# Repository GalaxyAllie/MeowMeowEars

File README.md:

# Meow Meow Ears

This is a project to create a pair of programmable neko mimis that feature ten LEDs.

## WARNINGS - *max power draw* and *brightness* and *health*

Please be aware that the LEDs can *easily* exceed the max power draw of this circuit design. It is highly recommended not to exceed 150 mA. They're cat ears, you don't need to blind everyone - keep the NeoPixel library brightness down to around 50 or so, tops :)

Also be aware some people are *photo sensitive* - these are meant for rave environments. For environments where people may not expect flashing lights (and where they do...) *please be considerate*.

## Basic Features

- ATSAMD21 microcontroller (ARM Cortext M0)
- Ten WS2812b RGB LEDs
- Power and status LEDs
- One capacitive touch zone - though this isn't used in the example code
- Native USB (you can even use it as a keyboard, hopefully)
- Designed to be put in cat ear headbands. Meow!
- Probably a fair number of bugs and bad design decisions!

## Copyright/Liability

I licence this work under [CC BY-SA 4.0](https://creativecommons.org/licenses/by-sa/4.0/#)

Also, I'm obviously not responsible for injuries or anything like that - this is definitely not a safety-tested, commercial project. Build at your own risk. It probably won't even work :)

## Build Notes

You really shouldn't draw over 50 mA or so of power, you're probably blinding people if you do :) - see warnings above. Thus, you should be fine to input all the way up to the linear regulator max voltage rating of 6V - but you're wasting energy over 3.3V. Thus, 3x NiMH batteries or a 3.7V Lion battery would be good power choices - be smart and sensible though. Batteries can be dangerous. There is no hardware over-discharge protection, so use only batteries with this protection!

Boards can be ordered from [Osh Park](https://oshpark.com/shared_projects/LssyuQtY) - that's not an affiliate link or anything, just a convenient source. And they're purple.

I have forked and modified the Adafruit Trinket M0 file from the Microsoft USB Mass Storage [Bootloader](https://github.com/MermaidAllie/uf2-samdx1/tree/master/build/alliecat_meowmeowears) for the ATSAMD21. The Trinket M0 bootloader also works, tho!

## Bill of Materials

| Component                               | Manufacturer                 | Qty |
|-----------------------------------------|------------------------------|-----|
| This board                              | Whoever you choose           | 1   |
| ATSAMD21E18A-AU-ND                      | Microchip Technology         | 1   |
| S2B-PH-SM4-TB(LF)(SN)                   | JST                          | 1   |
| 0.1uF 0603 Capacitor                    | Any                          | 10  |
| 1uF 0603 Capacitor                      | Any                          | 2   |
| 10uF 0603 Capacitor                     | Any                          | 2   |
| WS2812b LED                             | Worldsemi                    | 10  |
| UV/blacklight LED 0805 (or fave :) )    | Generic                      | 2   |
| AP2112K-3.3TRG1                         | Diodes Incorporated          | 1   |
| BAT54-TP                                | Micro Commercial Co          | 2   |
| USB3076-30-A                            | GCT                          | 1   |
| 510 Ohm 0805 Resistor (diff if UV sub)  | Any                          | 2   |
| 330 Ohm 0805 Resistor                   | Any                          | 1   |
| 3.5 x 6 mm push button switch           | Generic                      | 1   |

## Example Code

The example C++/Arduino code is designed to pretend the board is an Adafruit Trinket M0, and is for use with the Trinket M0 bootloader.

## Thanks

Thank you to the following people:

- Ladyada and [Adafruit](https://learn.adafruit.com/how-to-program-samd-bootloaders/trinket-m0-wiring) - for building excellent products and teaching people electronics. I used a lot of Trinket M0's in prototyping this. Seriously, people, go buy their products - they're fantastic (and the boards are way cuter than some others, especially look at the Metro M4 Express - it's just adorable).

- [OpenMoji](https://www.openmoji.org) - this is the source of the emoji used on the board silk.

- Q - for being an awesome friend who has helped with so much of the EDA side of working this all out. Thank you for answering late night messages with silly questions!

- JoJo Siwa - because the inspirational quote comes from one of your songs, and your concert on the [D.R.E.A.M. tour](https://www.jojodreamtour.com/) I went to in Cardiff was amazing. I'm not sure if it's your original quote tho, so I didn't quote it as you - I think I've heard it before? Either way, very inspiring performance! Keep things fun and positive and spread the positive energy, people!

## Version History

### v1

This was essentially a light strip on a cat ear shaped PCB.

### v2

This added an ATSAMD21 microcontroller.

### v3

This is the release version - it fixes the major bugs and makes them ready for general use.

### v3b

Minor update - reset on back where it's useful, more room to insert battery... not much else :)

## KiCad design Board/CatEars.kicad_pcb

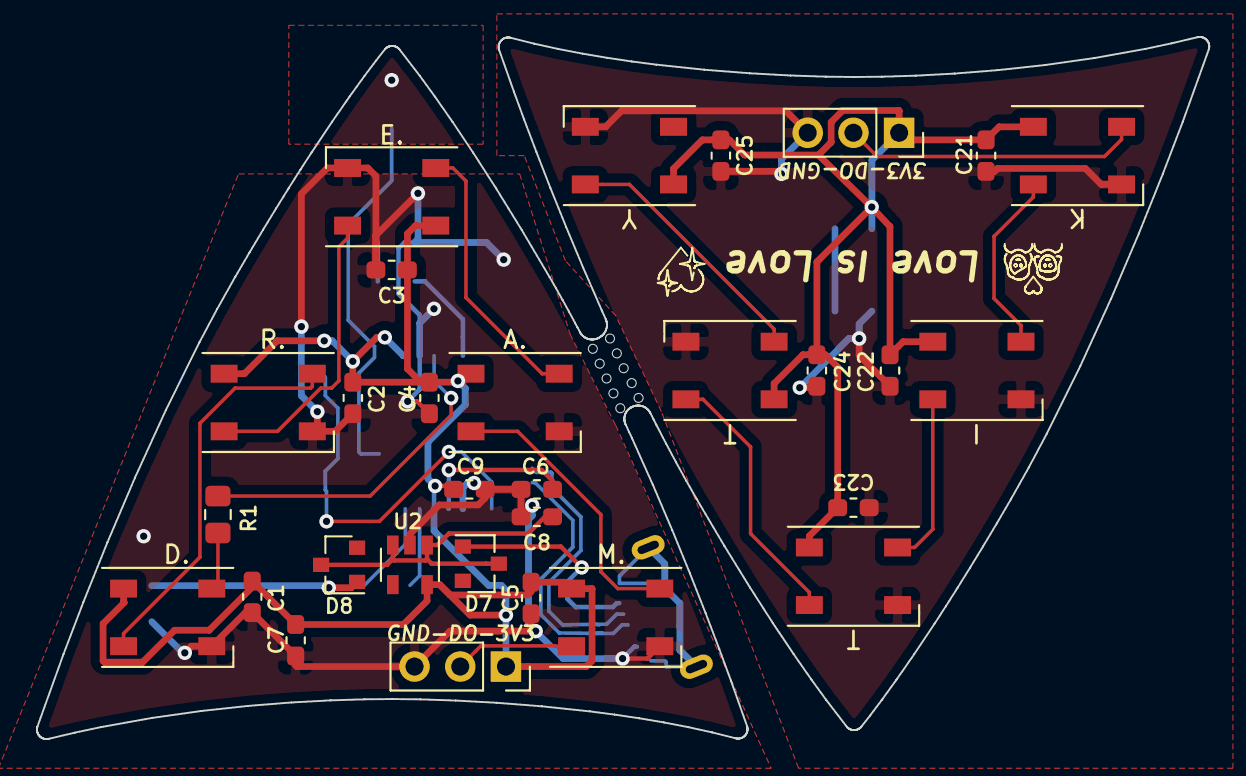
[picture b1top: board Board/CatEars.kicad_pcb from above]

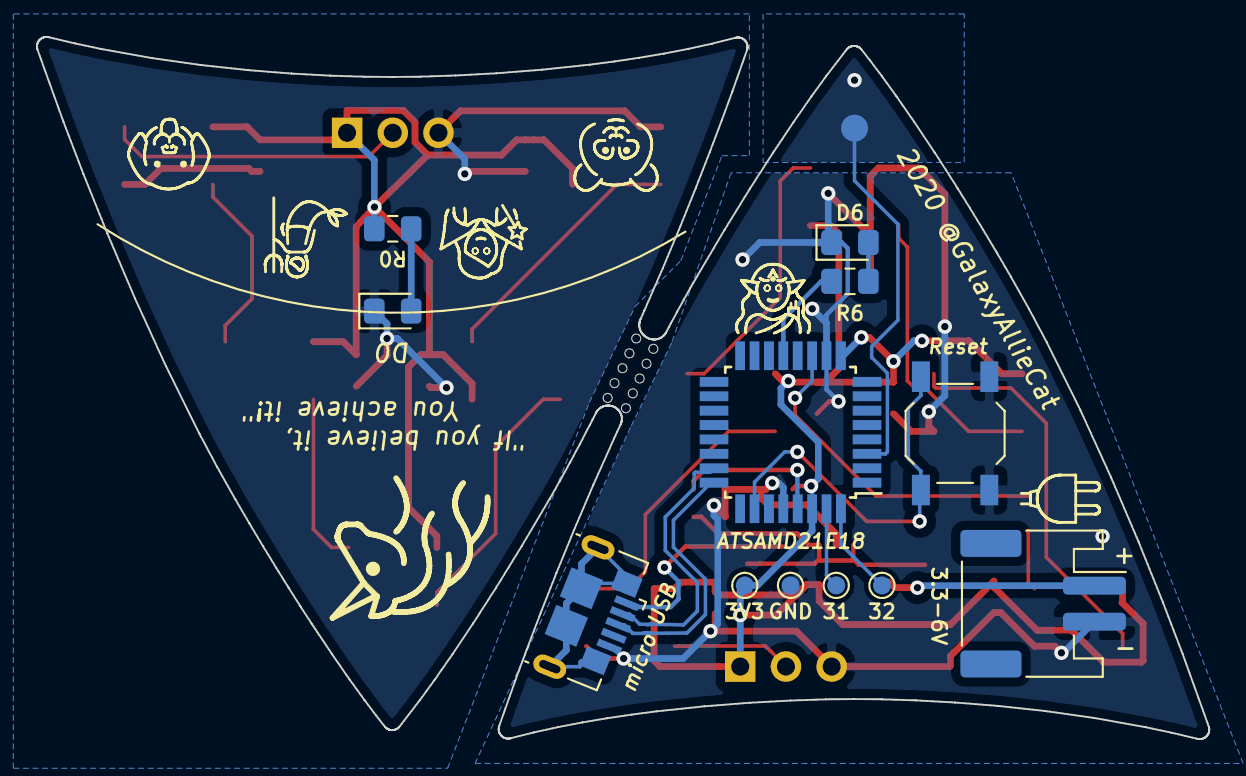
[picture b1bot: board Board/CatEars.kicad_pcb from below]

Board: 2 copper layers, 65.1 x 39.0 mm, 43 parts (13 on the bottom side), 29 nets.

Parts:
3V3, 31, 32: Conn_01x01; TestPoint_Pad_D1.0mm
3V3-DO-GND: Conn_01x03; PinSocket_1x03_P2.54mm_Vertical
A.: WS2812B; LED_WS2812B_PLCC4_5.0x5.0mm_P3.2mm
ATSAMD21E18: ATSAMD21E18A-AU; TQFP-32_7x7mm_P0.8mm
BT1: Battery; JST_PH_S2B-PH-SM4-TB_1x02-1MP_P2.00mm_Horizontal
C1, C2, C3, C4, C5, C21, C22, C23, C24, C25: 0.1 uF C; C_0603_1608Metric_Pad1.05x0.95mm_HandSolder
C6, C9: 1 uF C; C_0603_1608Metric_Pad1.05x0.95mm_HandSolder
C7, C8: 10 uF C; C_0603_1608Metric_Pad1.05x0.95mm_HandSolder
D0, D6: LED; LED_0805_2012Metric_Pad1.15x1.40mm_HandSolder
D7, D8: D_Schottky; D_SOT-23_ANK
D.: WS2812B; LED_WS2812B_PLCC4_5.0x5.0mm_P3.2mm
E.: WS2812B; LED_WS2812B_PLCC4_5.0x5.0mm_P3.2mm
GND: Conn_01x01; TestPoint_Pad_D1.0mm
GND-DO-3V3: Conn_01x03; PinSocket_1x03_P2.54mm_Vertical
H1: MountingHole_Pad; TestPoint_Pad_D1.5mm
I: WS2812B; LED_WS2812B_PLCC4_5.0x5.0mm_P3.2mm
K: WS2812B; LED_WS2812B_PLCC4_5.0x5.0mm_P3.2mm
M.: WS2812B; LED_WS2812B_PLCC4_5.0x5.0mm_P3.2mm
R0, R6: 510 R; R_0805_2012Metric_Pad1.15x1.40mm_HandSolder
R1: 330 R; R_0805_2012Metric_Pad1.15x1.40mm_HandSolder
R.: WS2812B; LED_WS2812B_PLCC4_5.0x5.0mm_P3.2mm
Reset: SW_Push; SW_SPST_TL3342
T: WS2812B; LED_WS2812B_PLCC4_5.0x5.0mm_P3.2mm
T#2: WS2812B; LED_WS2812B_PLCC4_5.0x5.0mm_P3.2mm
U2: AP2112K-3.3; SOT-23-5
Y: WS2812B; LED_WS2812B_PLCC4_5.0x5.0mm_P3.2mm
micro USB: USB_B_Micro; USB_Micro-B_GCT_USB3076-30-A

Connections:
+3V3: 3V3.1, A..1, ATSAMD21E18.9, ATSAMD21E18.30, C1.1, C2.1, C3.1, C4.1, C5.1, C7.2, C9.1, D..1, E..1, GND-DO-3V3.1, M..1, R..1, U2.5
+BATT: BT1.1, D8.2
/USB_D+: ATSAMD21E18.24, micro USB.3
/USB_D-: ATSAMD21E18.23, micro USB.2
GND: A..3, ATSAMD21E18.10, ATSAMD21E18.28, BT1.2, C1.2, C2.2, C3.2, C4.2, C5.2, C6.1, C7.1, C8.2, C9.2, D6.1, D..3, E..3, GND.1, GND-DO-3V3.3, M..3, R..3, Reset.2, U2.2, micro USB.5
unnamed: ATSAMD21E18.29, C6.2
unnamed: C8.1, D7.1, D8.1, U2.1, U2.3
unnamed: 3V3-DO-GND.1, C21.1, C22.1, C23.1, C24.1, C25.1, I.1, K.1, R0.2, T.1, T#2.1, Y.1
unnamed: 3V3-DO-GND.3, C21.2, C22.2, C23.2, C24.2, C25.2, D0.1, I.3, K.3, T.3, T#2.3, Y.3
unnamed: D0.2, R0.1
unnamed: D..2, R..4
unnamed: D..4, R1.2
unnamed: E..4, R..2
unnamed: A..4, E..2
unnamed: A..2, M..4
unnamed: GND-DO-3V3.2, M..2
unnamed: D6.2, R6.2
unnamed: I.4, K.2
unnamed: 3V3-DO-GND.2, K.4
unnamed: I.2, T.4
unnamed: T.2, T#2.4
unnamed: T#2.2, Y.4
unnamed: ATSAMD21E18.3, H1.1
unnamed: 31.1, ATSAMD21E18.31
unnamed: 32.1, ATSAMD21E18.32
unnamed: ATSAMD21E18.11, R1.1
unnamed: ATSAMD21E18.13, R6.1
unnamed: ATSAMD21E18.26, Reset.1
VBUS: D7.2, micro USB.1

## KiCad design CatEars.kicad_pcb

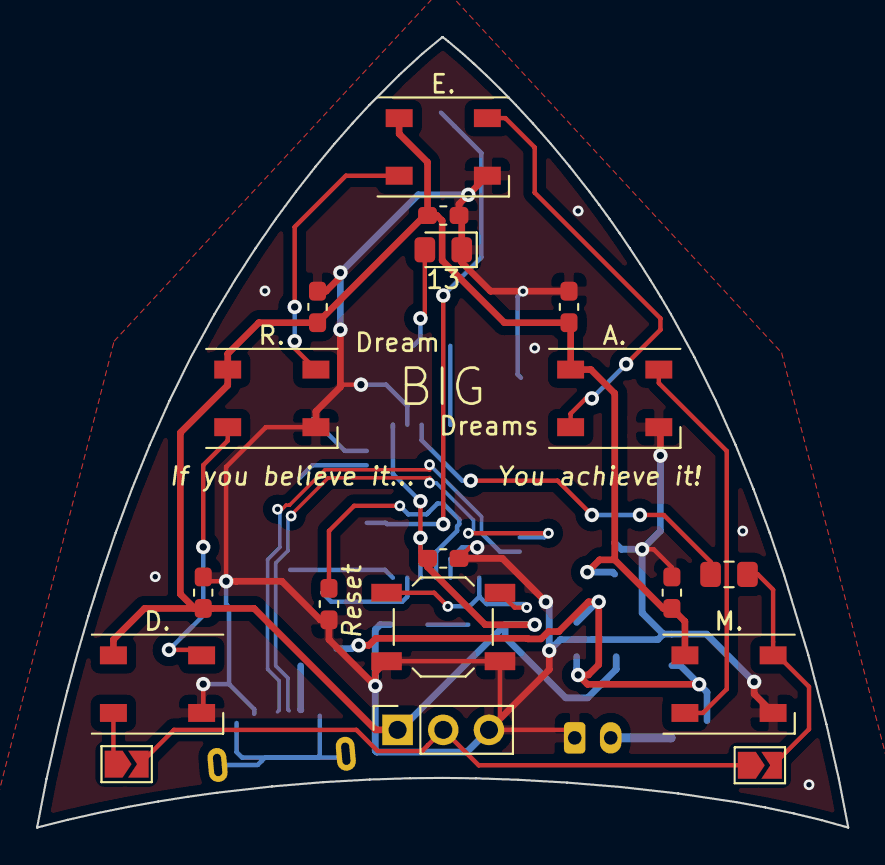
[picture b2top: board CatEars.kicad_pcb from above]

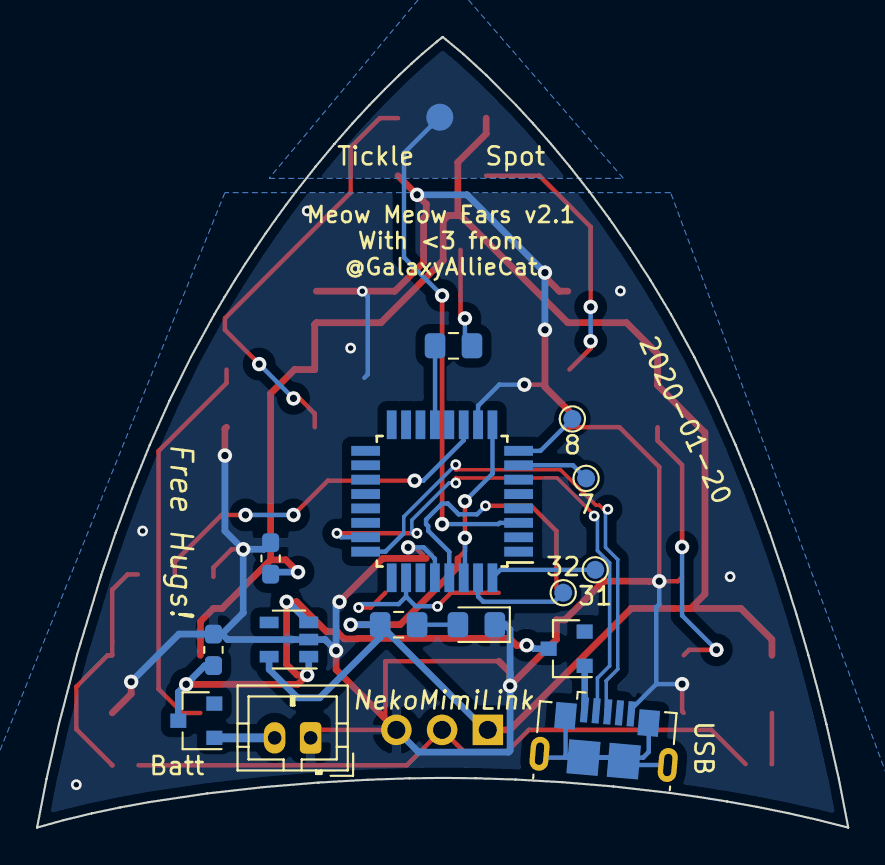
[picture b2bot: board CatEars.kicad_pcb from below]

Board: 2 copper layers, 45.1 x 43.9 mm, 34 parts (16 on the bottom side), 25 nets.

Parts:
7, 8, 31, 32: Conn_01x01; TestPoint_Pad_D1.0mm
13: LED; LED_0805_2012Metric_Pad1.15x1.40mm_HandSolder
A.: WS2812B; LED_WS2812B_PLCC4_5.0x5.0mm_P3.2mm
Batt: D_Schottky; D_SOT-23_ANK
C0, C1, C2, C3, C4, C5, C6, C7, C8: C; C_0603_1608Metric_Pad1.05x0.95mm_HandSolder
D6: LED; LED_0805_2012Metric_Pad1.15x1.40mm_HandSolder
D.: WS2812B; LED_WS2812B_PLCC4_5.0x5.0mm_P3.2mm
E.: WS2812B; LED_WS2812B_PLCC4_5.0x5.0mm_P3.2mm
H1: MountingHole_Pad; TestPoint_Pad_D1.5mm
J1: Conn_01x02_Male; JST_PH_B2B-PH-K_1x02_P2.00mm_Vertical
J2: USB_B_Micro; USB_Micro-B_GCT_USB3076-30-A
J3: Conn_01x03; PinSocket_1x03_P2.54mm_Vertical
JP1, JP2: SolderJumper_2_Open; SolderJumper-2_P1.3mm_Open_TrianglePad1.0x1.5mm
M.: WS2812B; LED_WS2812B_PLCC4_5.0x5.0mm_P3.2mm
R1, R2, R3: R; R_0805_2012Metric_Pad1.15x1.40mm_HandSolder
R.: WS2812B; LED_WS2812B_PLCC4_5.0x5.0mm_P3.2mm
Reset: SW_Push; SW_SPST_TL3342
U1: ATSAMD21E18A-AU; TQFP-32_7x7mm_P0.8mm
U2: AP2112K-3.3; SOT-23-5
USB: D_Schottky; D_SOT-23_ANK

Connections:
+3V3: A..1, C0.1, C1.1, C2.1, C3.1, C4.1, C6.1, C8.1, D..1, E..1, J3.1, M..1, R2.1, R..1, U1.9, U1.30, U2.5
+BATT: Batt.2, J1.2
/USB_D+: J2.3, U1.24
/USB_D-: J2.2, U1.23
GND: 13.1, A..3, C0.2, C1.2, C2.2, C3.2, C4.2, C5.1, C6.2, C7.2, C8.2, D6.1, D..3, E..3, J1.1, J2.5, J3.3, M..3, R..3, Reset.2, U1.10, U1.28, U2.2
unnamed: C5.2, U1.29
unnamed: Batt.1, C7.1, U2.1, U2.3, USB.1
unnamed: A..4, M..2
unnamed: JP2.2, M..4, R3.2
unnamed: A..2, E..4
unnamed: E..2, R..4
unnamed: D..4, R..2
unnamed: D..2, JP1.1
unnamed: 13.2, R1.2
unnamed: D6.2, R2.2
unnamed: H1.1, U1.3
unnamed: J3.2, JP1.2, JP2.1
unnamed: 32.1, U1.31
unnamed: 31.1, U1.32
unnamed: 8.1, U1.8
unnamed: 7.1, U1.7
unnamed: R1.1, U1.13
unnamed: R3.1, U1.11
unnamed: Reset.1, U1.26
VBUS: J2.1, USB.2

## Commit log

2020-01-10 Cat Ears v1
2020-01-11 Added schematic and copper
2020-01-12 Production Version with MCU - v2
2020-01-20 v2.1 - fix unconnected GND
2020-01-20 v2.1 - Minor silkscreen edit
2020-02-03 Added Board Outline
2020-02-04 Round corners panel
2020-02-04 FixedBoard
2020-02-06 v3 PCB final + gerbers
2020-02-07 remove old file
2020-02-10 Added twinkle mode + more comments
2020-02-10 Added more modes to sample code
    Also tested, all modes consume < 50 mA
2020-02-10 Release version
2020-02-10 Added license details
2020-02-11 Added Single Board Outline
2020-02-11 Fixed BOM
2020-02-19 Create LICENSE
2020-02-21 diffuser
2020-02-28 Capacitive touch enabled :D
2020-02-28 Fixed trans pride
2020-02-28 Move to PlatformIO
2020-02-28 Structure to allow for both versions in master
2020-02-28 Actual structure for MSP430 this time :)
2020-02-28 Create src - oops
2020-02-29 Only one version :)
2020-03-01 Custom board definition
    Sets correct USB hardware IDs
2020-03-02 Minor board design revision to allow more space to connect battery and easier assembly
2020-03-02 tiny tweaks, added new link + battery discharge warning
2020-03-02 New OSH Park link, rev notes, restored reset
2020-05-10 Update artwork readme
